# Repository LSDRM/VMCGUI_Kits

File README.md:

Resources for [VMCGUI](https://github.com/LSDRM/VMCGUI)
===============
----------
## Kits
### Arduino based :
No arduino based kit has been developed yet.

### Customized :
- [DualPressure - Thermocouple / through UART protocol](https://github.com/LSDRM/DualPressure-Thermocouple_forVMCGUI) : A DAQ board embeding two pressure sensors and one thermocouple. Developed by @B137P107

### Raspberry Pi based :
No raspberry pi based kit has been developed yet.

-------
## Modules
- [USB to UART bridge](https://github.com/LSDRM/USBtoUART-module_forVMCGUI) : To allow a computer the communicate through an UART communication line, via its USB port. Developed by @B137P107
--------

Make your own kit
=============
This repository include a _#BlankKit.py_ file which is a base to start making your own kit, working with VMCGUI. Making your own kit requires a bit of electronical knowledge, especially if you want to do it by making your own DAQ board (i.e. without an Arduino or other ready-to-use DAQ board). Creating a new kit implies software and hardware development, the both parts are described below.

Software development
-----------
You should only need to make a python kit file from the _#BlankKit.py_, without modifying any file from the source code of VMCGUI. The latter file need to be renamed with the name you want to give it, and placed in the "APP/Kits" folder of the VMCGUI repository. Note that the _#_ right before the name of your file set this kit as inactive, so  VMCGUI will ignore it.

At the top of your kit file, you should find the imported packages. This is where you can call new packages for your application. For example, you can call `import pyfirmata` if you know your kit is an Arduino-based one using an USB connection.

The first method of the main class contained in the kit file is the `__init__` one. In this class, you should find parameters for your kit as described below :
- `self.setWindowTitle()` : Put between the brackets the title of the window for your kit in string format.
- `self.prefix` : This parameter take a string, which gonna be placed right before the default name of the recorded files.
- `self.closeStartWindowOnLaunch` : Is set to `True` by default to prevent opening multiple times the same Kit Window, which risks to create conflict between multiple windows calling the same connection port.
- `self.graphTitle` : Is a list of strings containing the name of each sensor present with the DAQ board.
- `self.sensorsNumber` : Shall not be modified since it need to correspond the number of sensors name in `self.graphTitle`.
- `self.GPIOsNumber` : Take the number of accessible GPIOs on the DAQ board.

Hardware development
-----------
### Arduino

### Customized

### Raspberry Pi

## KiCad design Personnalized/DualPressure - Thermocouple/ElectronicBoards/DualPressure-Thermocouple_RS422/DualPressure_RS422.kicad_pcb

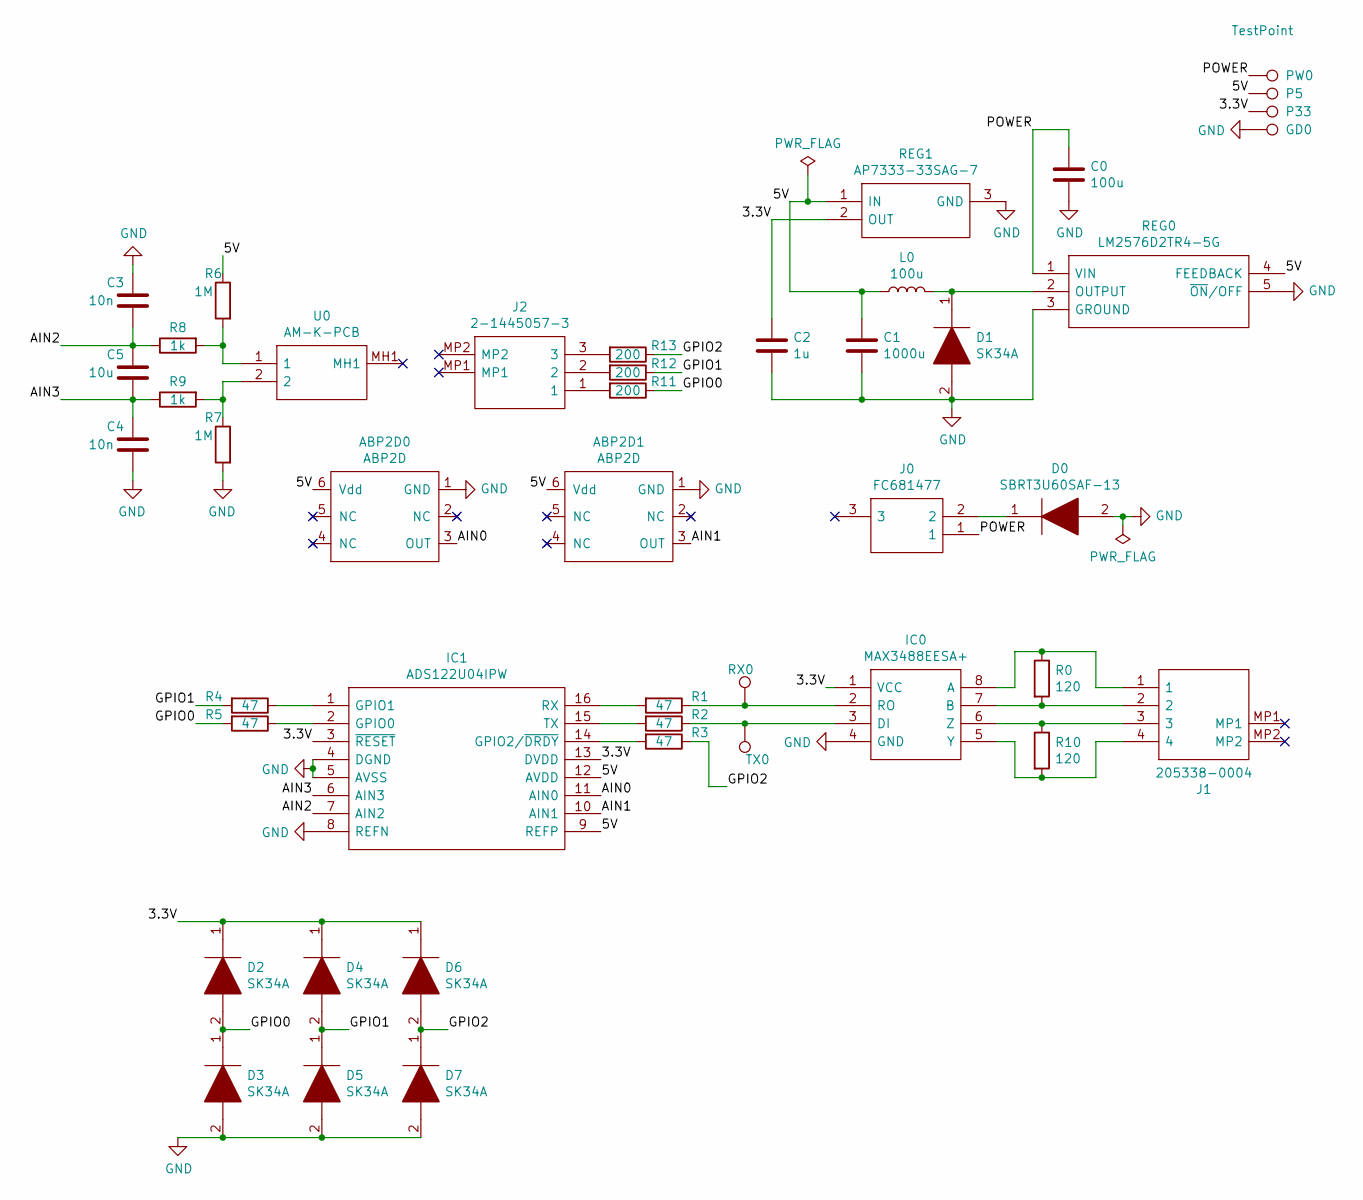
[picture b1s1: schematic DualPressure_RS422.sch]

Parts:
ABP2D0, ABP2D1: ABP2D
C0: 100u; CP_Elec_8x10.5
C1: 1000u; CP_Elec_10x10.5
C2: 1u; C_0603_1608Metric_Pad1.08x0.95mm_HandSolder
C3, C4: 10n; C_1206_3216Metric_Pad1.33x1.80mm_HandSolder
C5: 10u; C_1206_3216Metric_Pad1.33x1.80mm_HandSolder
D0: SBRT3U60SAF-13; SODFL5226X110N; Mouser Part Number 621-SBRT3U60SAF-13
D1, D2, D3, D4, D5, D6, D7: SK34A; DIOM5126X230N; Mouser Part Number 821-SK34A
GD0: TestPoint; TestPoint_THTPad_2.5x2.5mm_Drill1.2mm
IC0: MAX3488EESA+; SOIC127P600X175-8N; Mouser Part Number 700-MAX3488EESA
IC1: ADS122U04IPW; SOP65P640X120-16N; Mouser Part Number 595-ADS122U04IPW
J0: FC681477; Manufacturer_Part_Number FC681477
J1: 205338-0004; 2053380004; Manufacturer_Part_Number 205338-0004; Mouser Part Number 538-205338-0004
J2: 2-1445057-3; 214450573; Mouser Part Number 571-2-1445057-3
L0: 100u; L_0805_2012Metric_Pad1.15x1.40mm_HandSolder
P5, P33: TestPoint; TestPoint_THTPad_D2.5mm_Drill1.2mm
PW0: TestPoint; TestPoint_THTPad_D2.5mm_Drill1.2mm
R0, R10: 120; R_0805_2012Metric_Pad1.20x1.40mm_HandSolder
R1, R2, R3, R4, R5: 47; R_0805_2012Metric_Pad1.20x1.40mm_HandSolder
R6, R7: 1M; R_0805_2012Metric_Pad1.20x1.40mm_HandSolder
R8, R9: 1k; R_0805_2012Metric_Pad1.20x1.40mm_HandSolder
R11, R12, R13: 200; R_0805_2012Metric_Pad1.15x1.40mm_HandSolder
REG0: LM2576D2TR4-5G; D2TSUFFIX-CASE936A-02-ISSUEC; Mouser Part Number 863-LM2576D2TR4-5G
REG1: AP7333-33SAG-7; SOT96P240X135-3N; Mouser Part Number 621-AP7333-33SAG-7
RX0: TestPoint; TestPoint_THTPad_D2.5mm_Drill1.2mm
TX0: TestPoint; TestPoint_THTPad_D2.5mm_Drill1.2mm
U0: AM-K-PCB; AMKPCB; Manufacturer_Part_Number AM-K-PCB

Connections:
/3.3V: C2.1, D2.1, D4.1, D6.1, IC0.1 (VCC), IC1.3 (~RESET), IC1.13 (DVDD), P33.1, REG1.2 (OUT)
/5V: ABP2D0.6 (Vdd), ABP2D1.6 (Vdd), C1.1, IC1.9 (REFP), IC1.12 (AVDD), L0.1, P5.1, R6.1, REG0.4 (FEEDBACK), REG1.1 (IN)
/AIN0: ABP2D0.3 (OUT), IC1.11 (AIN0)
/AIN1: ABP2D1.3 (OUT), IC1.10 (AIN1)
/AIN2: C3.2, C5.1, IC1.7 (AIN2), R8.1
/AIN3: C4.1, C5.2, IC1.6 (AIN3), R9.1
/GPIO0: D2.2, D3.1, R5.2, R11.1
/GPIO1: D4.2, D5.1, R4.2, R12.1
/GPIO2: D6.2, D7.1, R3.1, R13.1
/POWER: C0.1, J0.1, PW0.1, REG0.1 (VIN)
GND: ABP2D0.1 (GND), ABP2D1.1 (GND), C0.2, C1.2, C2.2, C3.1, C4.2, D0.2, D1.2, D3.2, D5.2, D7.2, GD0.1, IC0.4 (GND), IC1.4 (DGND), IC1.5 (AVSS), IC1.8 (REFN), R7.2, REG0.3 (GROUND), REG0.5 (~ON~/OFF), REG0.6, REG1.3 (GND)
unnamed: D0.1, J0.2
unnamed: D1.1, L0.2, REG0.2 (OUTPUT)
unnamed: IC0.2 (RO), R1.1, RX0.1
unnamed: IC0.3 (DI), R2.1, TX0.1
unnamed: IC0.5 (Y), J1.4, R10.2
unnamed: IC0.6 (Z), J1.3, R10.1
unnamed: IC0.7 (B), J1.2, R0.2
unnamed: IC0.8 (A), J1.1, R0.1
unnamed: IC1.1 (GPIO1), R4.1
unnamed: IC1.2 (GPIO0), R5.1
unnamed: IC1.14 (GPIO2/~DRDY), R3.2
unnamed: IC1.15 (TX), R2.2
unnamed: IC1.16 (RX), R1.2
unnamed: J2.1, R11.2
unnamed: J2.2, R12.2
unnamed: J2.3, R13.2
unnamed: R6.2, R8.2, U0.1
unnamed: R7.1, R9.2, U0.2

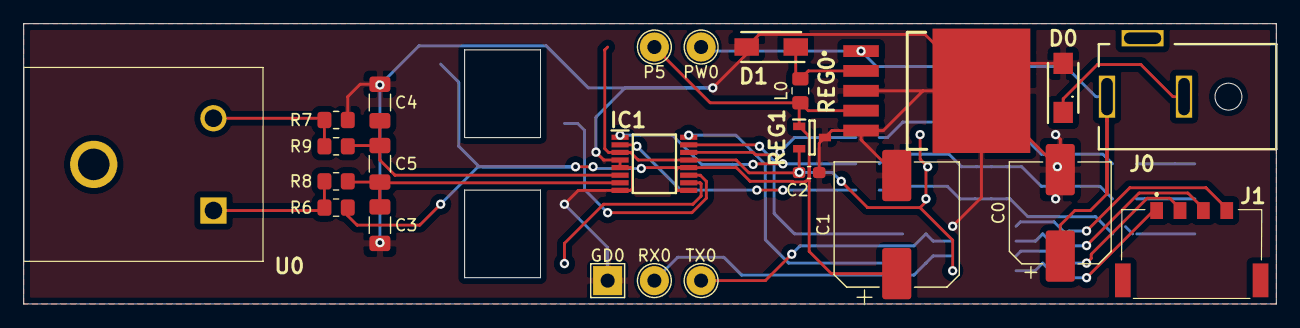
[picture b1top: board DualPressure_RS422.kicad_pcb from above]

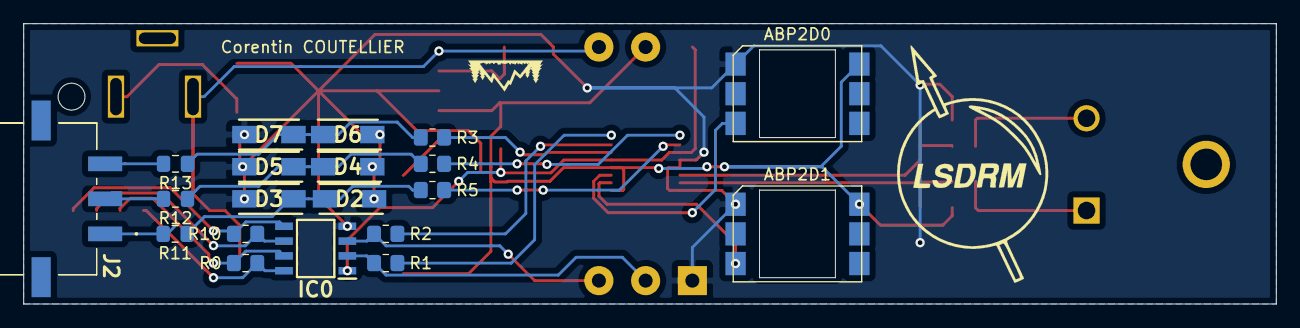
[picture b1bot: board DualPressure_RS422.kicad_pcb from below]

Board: 2 copper layers, 107.2 x 24.0 mm, 44 parts (20 on the bottom side), 29 nets.

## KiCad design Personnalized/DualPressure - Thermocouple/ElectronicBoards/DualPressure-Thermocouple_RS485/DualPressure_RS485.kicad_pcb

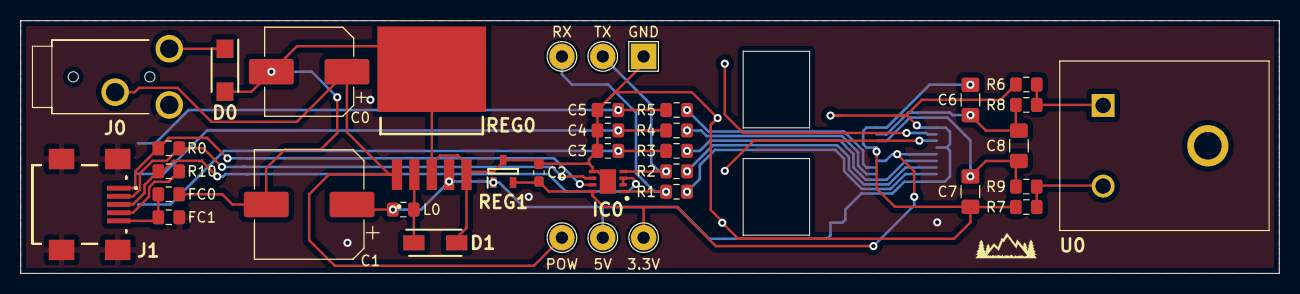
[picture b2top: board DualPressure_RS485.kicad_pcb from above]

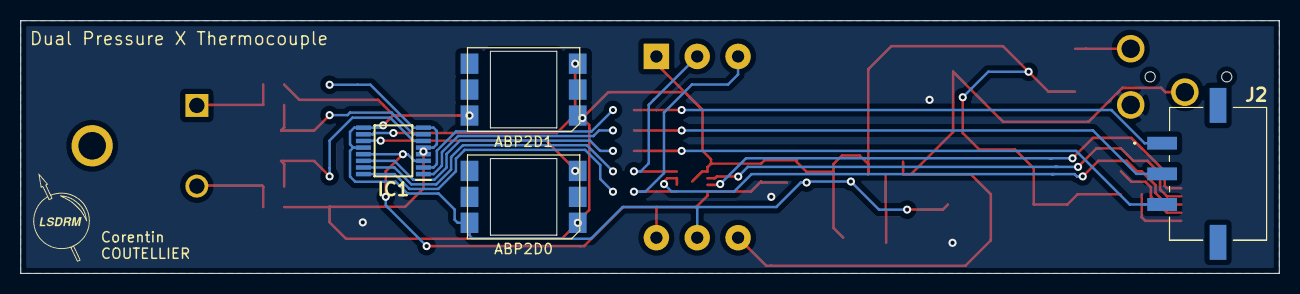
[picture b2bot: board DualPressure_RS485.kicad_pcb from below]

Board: 2 copper layers, 123.2 x 24.8 mm, 41 parts (4 on the bottom side), 28 nets.

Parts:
3.3V, 5V: TestPoint; TestPoint_THTPad_D2.5mm_Drill1.2mm
ABP2D0, ABP2D1: ABP2D
C0: 100u; CP_Elec_8x10.5
C1: 1000u; CP_Elec_10x10.5
C2: 1u; C_0603_1608Metric_Pad1.05x0.95mm_HandSolder
C3: FREECHOICE; C_0805_2012Metric_Pad1.15x1.40mm_HandSolder
C4, C5: FC; C_0805_2012Metric_Pad1.15x1.40mm_HandSolder
C6, C7: 10n; C_1206_3216Metric_Pad1.42x1.75mm_HandSolder
C8: 10u; C_1206_3216Metric_Pad1.42x1.75mm_HandSolder
D0: SBRT3U60SAF-13; SODFL5226X110N
D1: SK34A; DIOM5126X230N
FC0, FC1: R; R_0805_2012Metric_Pad1.15x1.40mm_HandSolder
GND: TestPoint; TestPoint_THTPad_2.5x2.5mm_Drill1.2mm
IC0: MAX14840EATA+; SON65P300X300X80-9N
IC1: ADS122U04IPW; SOP65P640X120-16N
J0: STX-3000; STX3000
J1: USB2066-05-RBHM-15-STB-00-00-A; USB206605RBHM15STB0000A
J2: 2-1445057-3; 214450573
L0: 100u; L_0805_2012Metric_Pad1.15x1.40mm_HandSolder
POW: TestPoint; TestPoint_THTPad_D2.5mm_Drill1.2mm
R0, R10: 120; R_0805_2012Metric_Pad1.15x1.40mm_HandSolder
R1, R2, R3, R4, R5: 47; R_0805_2012Metric_Pad1.15x1.40mm_HandSolder
R6, R7: 1M; R_0805_2012Metric_Pad1.15x1.40mm_HandSolder
R8, R9: 1k; R_0805_2012Metric_Pad1.15x1.40mm_HandSolder
REG0: LM2576D2TR4-5G; D2TSUFFIX-CASE936A-02-ISSUEC
REG1: AP7333-33SAG-7; SOT96P240X135-3N
RX: TestPoint; TestPoint_THTPad_D2.5mm_Drill1.2mm
TX: TestPoint; TestPoint_THTPad_D2.5mm_Drill1.2mm
U0: AM-K-PCB; AMKPCB

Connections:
/3.3V: 3.3V.1, C2.1, IC0.8, IC1.3, IC1.13, REG1.2
/5V: 5V.1, ABP2D0.6, ABP2D1.6, C1.1, IC1.9, IC1.12, L0.1, R6.1, REG0.4, REG1.1
/#ENABLE: IC0.2, IC0.3, J1.3, R10.1
/AIN0: ABP2D0.3, IC1.11
/AIN1: ABP2D1.3, IC1.10
/AIN2: C6.2, C8.1, IC1.7, R8.1
/AIN3: C7.1, C8.2, IC1.6, R9.1
/ENABLE: J1.4, R10.2
/GPIO0: C5.1, J2.1, R5.2
/GPIO1: C4.1, J2.2, R4.2
/GPIO2: C3.1, J2.3, R3.1
/POWER: C0.1, J0.1, POW.1, REG0.1
/SHIELD: FC1.2, J0.3, J1.MP1, J1.MP2, J1.MP3, J1.MP4
GND: ABP2D0.1, ABP2D1.1, C0.2, C1.2, C2.2, C3.2, C4.2, C5.2, C6.1, C7.2, D0.2, D1.2, FC0.2, GND.1, IC0.5, IC0.9, IC1.4, IC1.5, IC1.8, R7.2, REG0.3, REG0.5, REG0.6, REG1.3
unnamed: D0.1, J0.2
unnamed: D1.1, L0.2, REG0.2
unnamed: FC0.1, FC1.1, J1.5
unnamed: IC0.1, R1.1, RX.1
unnamed: IC0.4, R2.1, TX.1
unnamed: IC0.6, J1.2, R0.2
unnamed: IC0.7, J1.1, R0.1
unnamed: IC1.1, R4.1
unnamed: IC1.2, R5.1
unnamed: IC1.14, R3.2
unnamed: IC1.15, R2.2
unnamed: IC1.16, R1.2
unnamed: R6.2, R8.2, U0.1
unnamed: R7.1, R9.2, U0.2

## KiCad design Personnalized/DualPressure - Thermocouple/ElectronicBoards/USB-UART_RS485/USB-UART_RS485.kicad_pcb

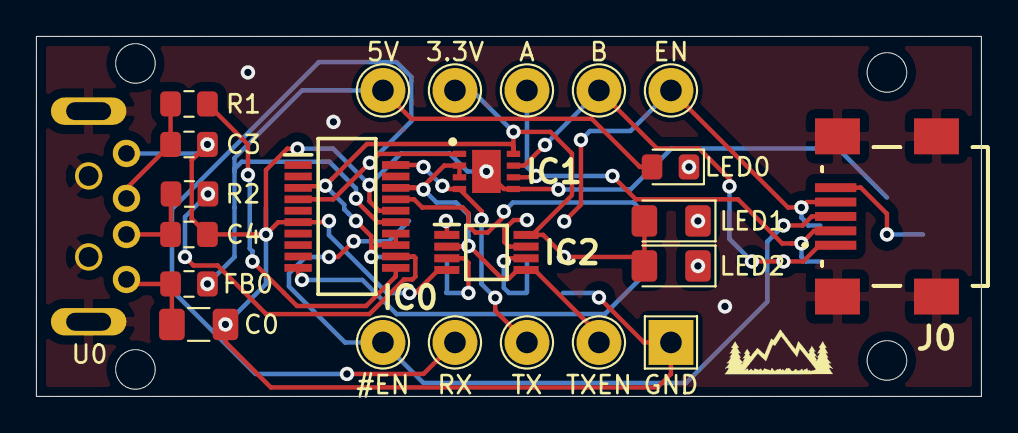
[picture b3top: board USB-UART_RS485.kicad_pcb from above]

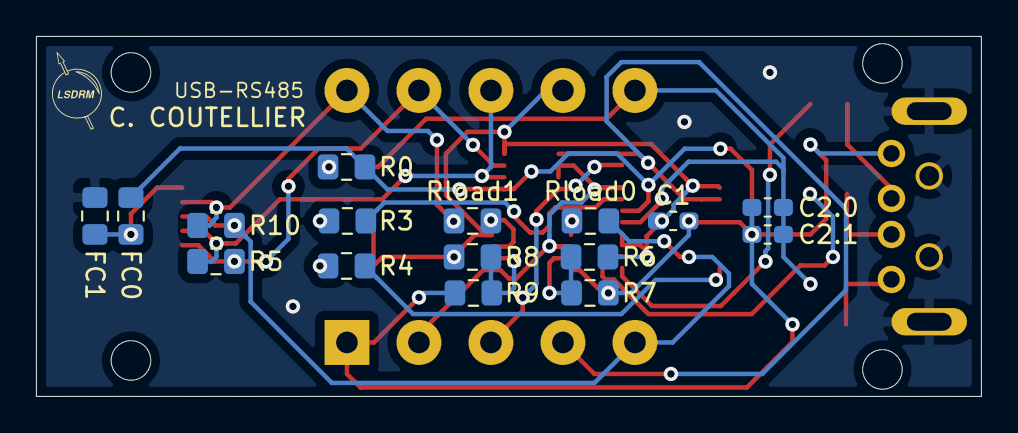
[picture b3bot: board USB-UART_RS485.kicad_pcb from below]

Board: 2 copper layers, 52.5 x 20.0 mm, 39 parts (16 on the bottom side), 26 nets.

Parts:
3.3V, 5V: TestPoint; TestPoint_THTPad_D2.5mm_Drill1.2mm
A: TestPoint; TestPoint_THTPad_D2.5mm_Drill1.2mm
B: TestPoint; TestPoint_THTPad_D2.5mm_Drill1.2mm
C0: 10n; C_1206_3216Metric_Pad1.42x1.75mm_HandSolder
C1, C2.1: 0.1u; C_0603_1608Metric_Pad1.05x0.95mm_HandSolder
C2.0: 4.7u; C_0603_1608Metric_Pad1.05x0.95mm_HandSolder
C3, C4: 47p; C_0805_2012Metric_Pad1.15x1.40mm_HandSolder
EN: TestPoint; TestPoint_THTPad_D2.5mm_Drill1.2mm
FB0: Ferrite_Bead_Small; L_0805_2012Metric_Pad1.15x1.40mm_HandSolder
FC0, FC1: R; R_0805_2012Metric_Pad1.15x1.40mm_HandSolder
GND: TestPoint; TestPoint_THTPad_2.5x2.5mm_Drill1.2mm
IC0: FT231XS-R; SOP64P599X175-20N
IC1: MAX14840EATA+; SON65P300X300X80-9N
IC2: NCS20032DMR2G; SOP65P490X110-8N
J0: USB2066-05-RBHM-15-STB-00-00-A; USB206605RBHM15STB0000A
LED0: LG R971; LED_0805_2012Metric_Pad1.15x1.40mm_HandSolder
LED1, LED2: KP-3216SURC; LED_1206_3216Metric_Pad1.42x1.75mm_HandSolder
R0: 130; R_0805_2012Metric_Pad1.15x1.40mm_HandSolder
R1, R2: 27; R_0805_2012Metric_Pad1.15x1.40mm_HandSolder
R3, R4: 68; R_0805_2012Metric_Pad1.15x1.40mm_HandSolder
R5, R10: 120; R_0805_2012Metric_Pad1.15x1.40mm_HandSolder
R6, R7, R8, R9: 1M; R_0805_2012Metric_Pad1.15x1.40mm_HandSolder
RX: TestPoint; TestPoint_THTPad_D2.5mm_Drill1.2mm
Rload0, Rload1: 10k; R_0805_2012Metric_Pad1.15x1.40mm_HandSolder
TX: TestPoint; TestPoint_THTPad_D2.5mm_Drill1.2mm
TXEN: TestPoint; TestPoint_THTPad_D2.5mm_Drill1.2mm
U0: MC32603

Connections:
/3.3V: 3.3V.1, C1.1, IC0.3, IC0.13, IC0.14, IC1.8, IC2.8, LED1.2, LED2.2, R6.2, R8.1
/5V: 5V.1, C2.0.1, C2.1.1, FB0.1, IC0.15, LED0.2
/#ENABLE: J0.3, R10.1, Rload0.2
/D+: C3.2, R1.2, U0.3
/D-: C4.1, R2.2, U0.2
/ENABLE: EN.1, J0.4, R10.2, Rload1.1
/SHIELD: FC1.2, J0.MP1, J0.MP2, J0.MP3, J0.MP4, U0.5
/TXDEN: IC0.18, IC1.2, IC1.3, IC2.2, IC2.5, TXEN.1
GND: C0.2, C1.2, C2.0.2, C2.1.2, C3.1, C4.2, FC0.2, GND.1, IC0.6, IC0.16, IC1.5, IC1.9, IC2.4, R0.1, R7.2, R9.2, U0.4
unnamed: A.1, IC1.6, J0.2, R5.2
unnamed: B.1, IC1.7, J0.1, R5.1
unnamed: C0.1, FB0.2, U0.1
unnamed: FC0.1, FC1.1, J0.5
unnamed: IC0.4, IC1.1, RX.1
unnamed: IC0.10, R4.1
unnamed: IC0.11, R1.1
unnamed: IC0.12, R2.1
unnamed: IC0.17, R3.1
unnamed: IC0.20, IC1.4, TX.1
unnamed: IC2.1, Rload0.1
unnamed: IC2.3, R6.1, R7.1
unnamed: IC2.6, R8.2, R9.1
unnamed: IC2.7, Rload1.2
unnamed: LED0.1, R0.2
unnamed: LED1.1, R3.2
unnamed: LED2.1, R4.2

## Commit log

2024-01-05 Updated whole repository
